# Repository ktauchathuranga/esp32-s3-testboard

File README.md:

# ESP32-S3 Test Board

A custom-designed development board for the ESP32-S3, designed in KiCad. This project was created for learning and prototyping purposes, featuring USB-C connectivity and a compact form factor.

## About The Project

This PCB is a breakout and test board for the **ESP32-S3** microcontroller. It breaks out the necessary pins for prototyping and includes essential circuitry for power management and programming.

The design is based on the [High Speed PCB Design tutorial by Made by Morten](https://www.youtube.com/watch?v=QoU0WWNgO2g).

### Key Features
* **Microcontroller:** ESP32-S3 (WROOM Module)
* **Connectivity:** USB Type-C (Native USB)
* **Power:** Onboard 3.3V LDO Regulator
* **User Interface:** Reset & Boot buttons, Status LEDs
* **Layer Stack:** 4-Layer PCB design for better signal integrity and power distribution

## EDA Tool & Libraries

* **Designed in:** [KiCad EDA](https://www.kicad.org/)
* **Custom Library:** This project utilizes specific footprints and symbols from my personal library:
    * [Oddibits - KiCad Library](https://github.com/ktauchathuranga/oddibits)

## Getting Started

To view or modify the design:

1.  Clone this repository:
    ```bash
    git clone https://github.com/ktauchathuranga/esp32-s3-testboard.git
    ```
2.  Clone the dependency library (Oddibits) alongside it or add it to your KiCad Global Libraries table:
    ```bash
    git clone https://github.com/ktauchathuranga/oddibits.git
    ```
3.  Open the `.kicad_pro` file in KiCad 7.0 or later.

## Fabrication

This board is designed to be manufactured by standard PCB fabrication houses (e.g., JLCPCB, PCBWay).
* **Layers:** 4
* **Minimum Trace/Space:** Check Design Rules (usually 0.2mm or similar standard capabilities)
* **Via Size:** Standard

## Credits & References

* **Original Guide:** [Made by Morten - ESP32-S3 PCB Design](https://www.youtube.com/watch?v=QoU0WWNgO2g)
* **Espressif Systems:** For the ESP32-S3 Datasheets and Hardware Design Guidelines.

## License

This project is open-source. Please see the [LICENSE](LICENSE) file for more details.

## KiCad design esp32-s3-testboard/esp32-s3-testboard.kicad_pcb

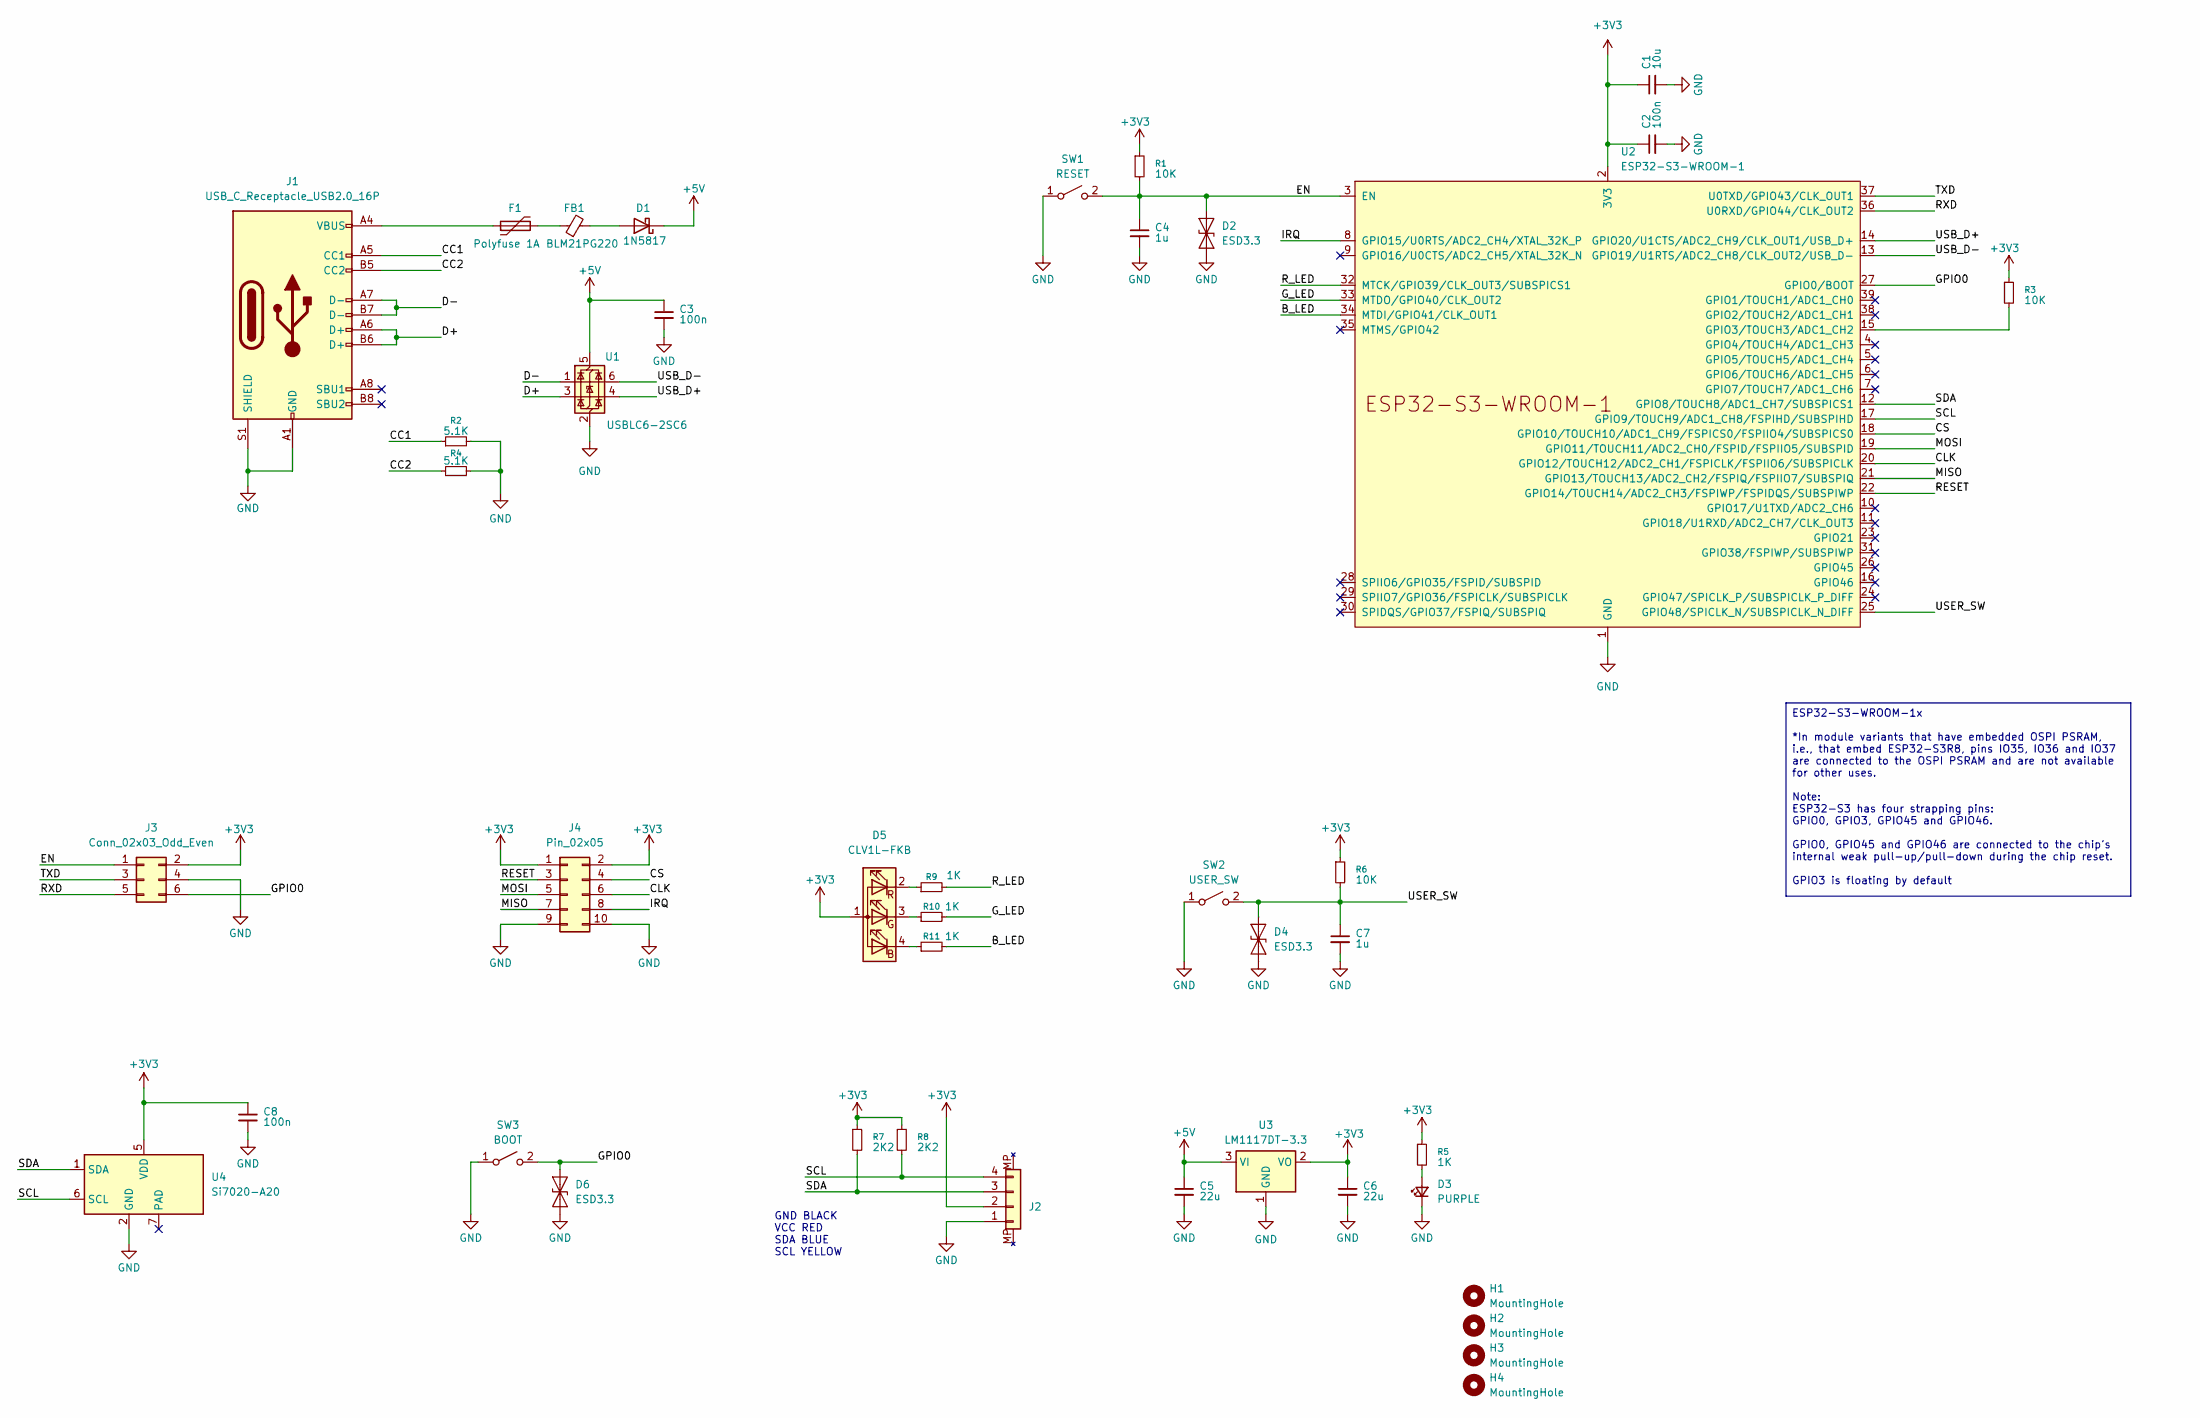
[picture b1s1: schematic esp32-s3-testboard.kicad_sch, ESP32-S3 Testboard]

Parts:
C1: 10u; C_0603_1608Metric
C2, C3, C8: 100n; C_0402_1005Metric
C4, C7: 1u; C_0603_1608Metric
C5, C6: 22u; C_0805_2012Metric
D1: 1N5817; D_SOD-123
D2, D4, D6: ESD3.3; D_SOD-923
D3: PURPLE; LED_0603_1608Metric
D5: CLV1L-FKB; LED_Cree-PLCC4_3.2x2.8mm_CCW
F1: Polyfuse 1A; Fuse_1206_3216Metric
FB1: BLM21PG220; L_0805_2012Metric
H1, H2, H3, H4: MountingHole; MountingHole_3.2mm_M3
J1: USB_C_Receptacle_USB2.0_16P; USB_C_Receptacle_GCT_USB4105-xx-A_16P_TopMnt_Horizontal
J2: JST_SH_SM04B-SRSS-TB_1x04-1MP_P1.00mm_Horizontal
J3: Conn_02x03_Odd_Even; PinHeader_2x03_P2.54mm_Vertical
J4: Pin_02x05; PinHeader_2x05_P2.54mm_Vertical
R1, R3, R6: 10K; R_0402_1005Metric
R2, R4: 5.1K; R_0402_1005Metric
R5, R9, R10, R11: 1K; R_0402_1005Metric
R7, R8: 2K2; R_0402_1005Metric
SW1: RESET; SW_SPST_B3U-1100P
SW2: USER_SW; SW_Tactile_SPST_Angled_PTS645Vx31-2LFS
SW3: BOOT; SW_SPST_B3U-1100P
U1: USBLC6-2SC6; SOT-23-6
U2: ESP32-S3-WROOM-1
U3: LM1117DT-3.3; SOT-223-3_TabPin2
U4: Si7020-A20; DFN-6-1EP_3x3mm_P1mm_EP1.5x2.4mm

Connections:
+3V3: C1.1, C2.1, C6.1, C8.1, D5.1 (A), J2.2, J3.2, J4.1, J4.2, R1.1, R3.1, R5.1, R6.1, R7.1, R8.1, U2.2 (3V3), U3.2 (VO), U4.5 (VDD); also elsewhere on the board
+5V: C3.1, C5.1, D1.1 (K), U1.5 (VBUS), U3.3 (VI)
/B_LED: R11.2, U2.34 (MTDI/GPIO41/CLK_OUT1)
/CC1: J1.A5 (CC1), R2.1
/CC2: J1.B5 (CC2), R4.1
/CLK: J4.6, U2.20 (GPIO12/TOUCH12/ADC2_CH1/FSPICLK/FSPIIO6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)
/CS: J4.4, U2.18 (GPIO10/TOUCH10/ADC1_CH9/FSPICS0/FSPIIO4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)
/D+: J1.A6 (D+), J1.B6 (D+), U1.3 (I/O2)
/D-: J1.A7 (D-), J1.B7 (D-), U1.1 (I/O1)
/EN: C4.1, D2.2 (A2), J3.1, R1.2, SW1.2 (B), U2.3 (EN); also elsewhere on the board
/GPIO0: D6.2 (A2), J3.6, SW3.2 (B), U2.27 (GPIO0/BOOT); also elsewhere on the board
/G_LED: R10.2, U2.33 (MTDO/GPIO40/CLK_OUT2)
/IRQ: J4.8, U2.8 (GPIO15/U0RTS/ADC2_CH4/XTAL_32K_P)
/MISO: J4.7, U2.21 (GPIO13/TOUCH13/ADC2_CH2/FSPIQ/FSPIIO7/S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)
/MOSI: J4.5, U2.19 (GPIO11/TOUCH11/ADC2_CH0/FSPID/FSPIIO5/S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)
/RESET: J4.3, U2.22 (GPIO14/TOUCH14/ADC2_CH3/FSPIWP/FSPIDQS/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)
/RXD: J3.5, U2.36 (U0RXD/GPIO44/CLK_OUT2); also elsewhere on the board
/R_LED: R9.2, U2.32 (MTCK/GPIO39/CLK_OUT3/SUBSPICS1)
/SCL: J2.4, R8.2, U2.17 (GPIO9/TOUCH9/ADC1_CH8/FSPIHD/SUBSPIHD), U4.6 (SCL)
/SDA: J2.3, R7.2, U2.12 (GPIO8/TOUCH8/ADC1_CH7/SUBSPICS1), U4.1 (SDA)
/TXD: J3.3, U2.37 (U0TXD/GPIO43/CLK_OUT1); also elsewhere on the board
/USB_D+: U1.4 (I/O2), U2.14 (GPIO20/U1CTS/ADC2_CH9/CLK_OUT1/USB_D+)
/USB_D-: U1.6 (I/O1), U2.13 (GPIO19/U1RTS/ADC2_CH8/CLK_OUT2/USB_D-)
/USER_SW: C7.1, D4.2 (A2), R6.2, SW2.2 (B), U2.25 (GPIO48/SPICLK_N/SUBSPICLK_N_DIFF)
GND: C1.2, C2.2, C3.2, C4.2, C5.2, C6.2, C7.2, C8.2, D2.1 (A1), D3.1 (K), D4.1 (A1), D6.1 (A1), J1.A1 (GND), J1.A12 (GND), J1.B1 (GND), J1.B12 (GND), J1.S1 (SHIELD), J2.1, J3.4, J4.9, J4.10, R2.2, R4.2, SW1.1 (A), SW2.1 (A), SW3.1 (A), U1.2 (GND), U2.1 (GND), U2.40 (GND), U2.41 (GND), U3.1 (GND), U4.2 (GND); also elsewhere on the board
unnamed: D1.2 (A), FB1.2
unnamed: D3.2 (A), R5.2
unnamed: D5.4 (BK), R11.1
unnamed: D5.3 (GK), R10.1
unnamed: D5.2 (RK), R9.1
unnamed: F1.1, J1.A4 (VBUS), J1.A9 (VBUS), J1.B4 (VBUS), J1.B9 (VBUS)
unnamed: F1.2, FB1.1
unnamed: R3.2, U2.15 (GPIO3/TOUCH3/ADC1_CH2)

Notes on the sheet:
GND BLACK VCC RED SDA BLUE SCL YELLOW
ESP32-S3-WROOM-1x *In module variants that have embedded OSPI PSRAM, i.e., that embed ESP32-S3R8, pins IO35, IO36 and IO37 are connected to the OSPI PSRAM and are not available for other uses. Note: ESP32-S3 has four strapping pins: GPIO0, GPIO3, GPIO45 and GPIO46. GPIO0, GPIO45 and GPIO46 are conn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

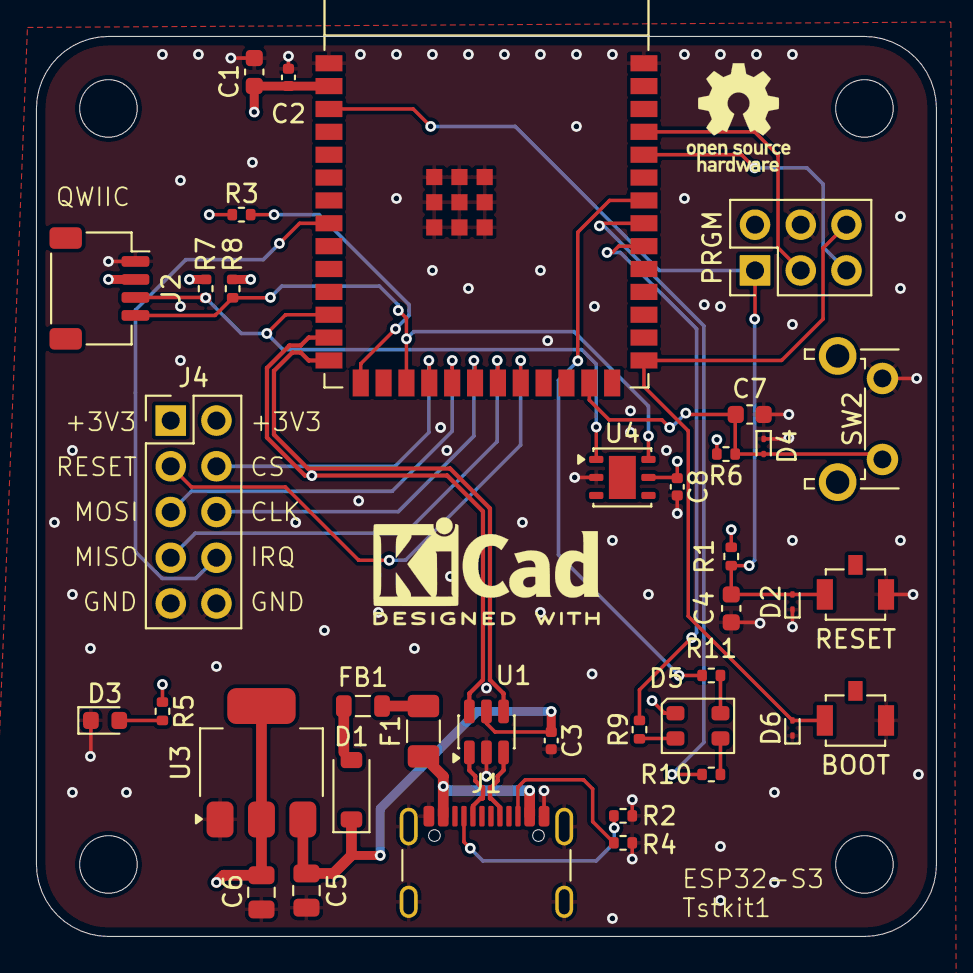
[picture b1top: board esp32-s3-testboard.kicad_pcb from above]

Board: 4 copper layers, 50.0 x 50.0 mm, 42 parts (0 on the bottom side), 33 nets.

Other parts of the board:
BOOT: BOOT; SW_SPST_B3U-1100P
PRGM: Conn_02x03_Odd_Even; PinHeader_2x03_P2.54mm_Vertical
RESET: RESET; SW_SPST_B3U-1100P

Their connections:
+3V3: PRGM.2; also elsewhere on the board
/EN: PRGM.1, RESET.2 (B); also elsewhere on the board
/GPIO0: BOOT.2 (B), PRGM.6; also elsewhere on the board
/RXD: PRGM.5; also elsewhere on the board
/TXD: PRGM.3; also elsewhere on the board
GND: BOOT.1 (A), PRGM.4, RESET.1 (A); also elsewhere on the board

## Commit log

2026-01-04 sch complete
2026-01-04 completeddd
2026-01-04 touches
2026-01-04 docccc
2026-01-04 doccccccccccccc
2026-01-04 Add MIT License to the project
2026-01-04 doc fix
